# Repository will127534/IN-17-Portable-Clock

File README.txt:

This is a project of my NIXIE Clock
which uses four IN-17 in a 5cm x 3 cm size
and it can power by USB and build in 200mah Li-poly.

Blog(Chinese):http://will-123456.blogspot.tw/2015/03/in-17-nixie-tube-portable-clock.html
Hackaday.io :http://hackaday.io/project/5105-in-17-portable-clock

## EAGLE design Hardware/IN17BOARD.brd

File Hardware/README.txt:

Becareful about High Voltage and Li-poly battery

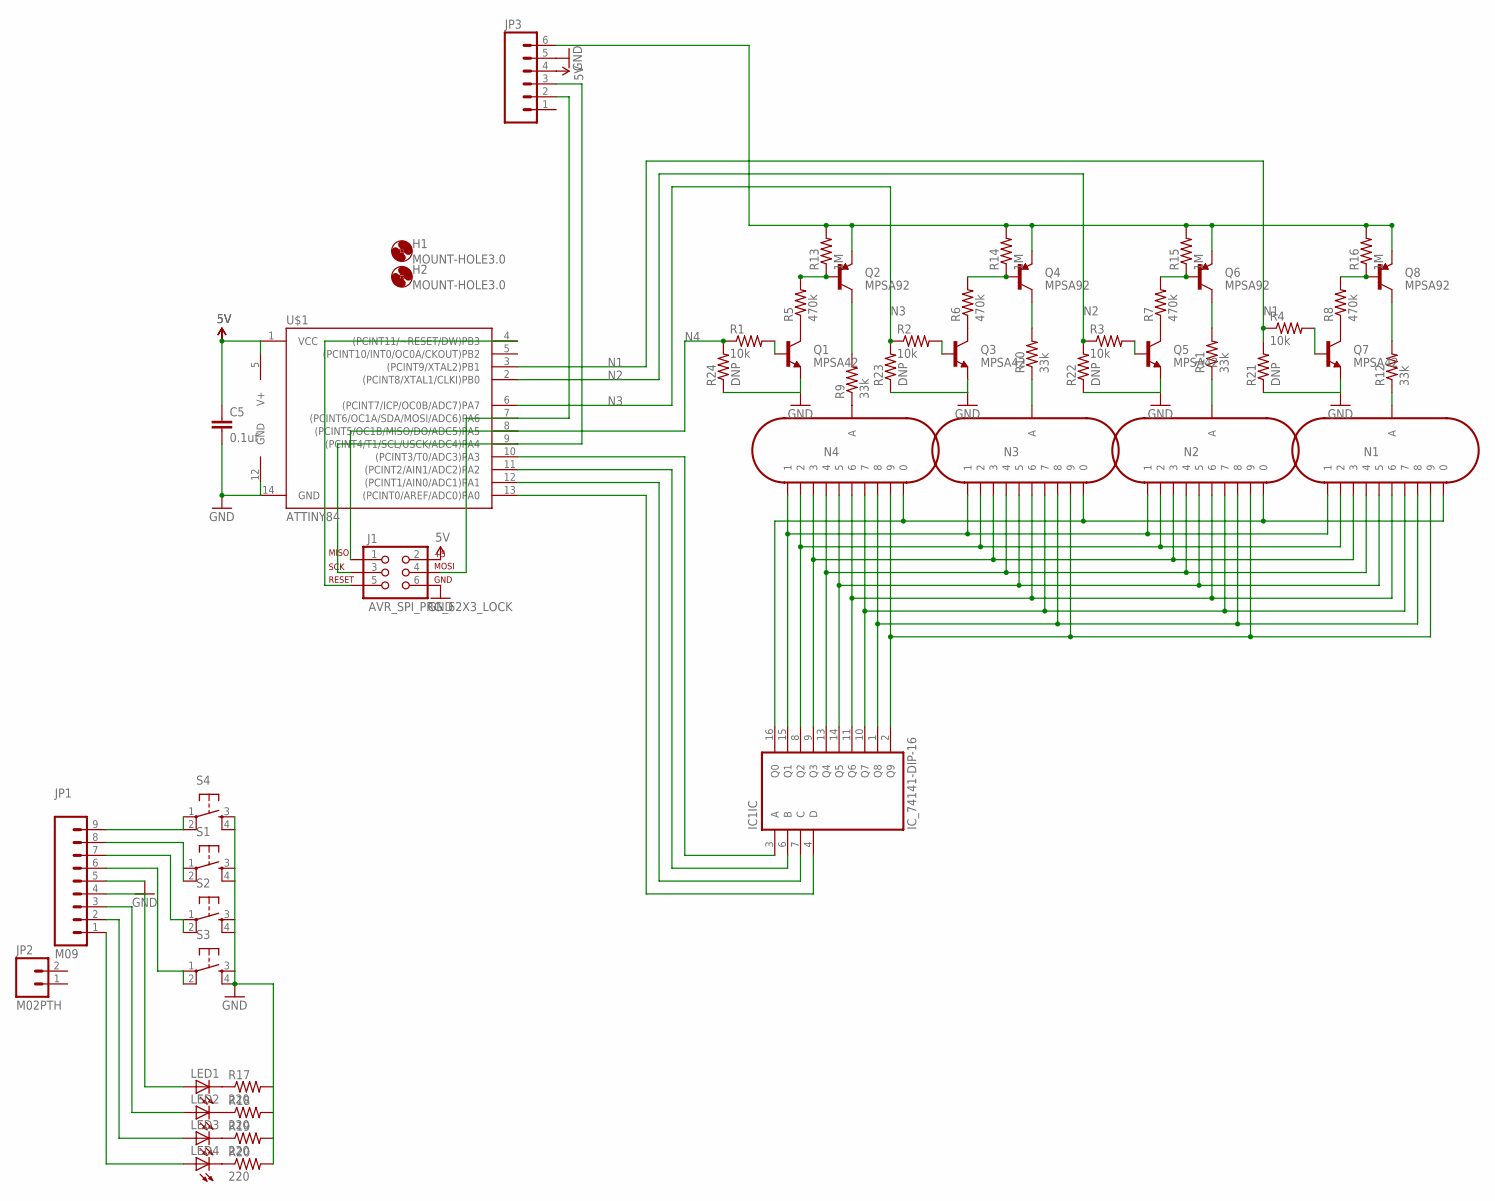
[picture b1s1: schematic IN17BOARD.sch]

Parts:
C5: 0.1uf; 0805
H1, H2: MOUNT-HOLE3.0; 3,0
IC1: IC_74141-DIP-16; DIL16
J1: AVR_SPI_PRG_62X3_LOCK; 2X3_LOCK
JP1: M09; 1X09
JP2: M02PTH; 1X02
JP3: M06SIP; 1X06
LED1, LED2, LED3, LED4: LED0603; LED-0603
N1, N2, N3, N4: IN-17
Q1, Q3, Q5, Q7: MPSA42; SOT23
Q2, Q4, Q6, Q8: MPSA92; SOT23
R1, R2, R3, R4: 10k; 0805
R5, R6, R7, R8: 470k; 0805
R9, R10, R11, R12: 33k; 0805
R13, R14, R15, R16: 1M; 0805
R17, R18, R19, R20: 220; 0603-RES
R21, R22, R23, R24: DNP; 0805
S1, S2, S3, S4: TAC_SWITCHPTH; TACTILE-PTH
U$1: ATTINY84; SO14

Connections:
0: IC1.16 (Q0), N1.0, N2.0, N3.0, N4.0
1: IC1.15 (Q1), N1.1, N2.1, N3.1, N4.1
2: IC1.8 (Q2), N1.2, N2.2, N3.2, N4.2
3: IC1.9 (Q3), N1.3, N2.3, N3.3, N4.3
4: IC1.13 (Q4), N1.4, N2.4, N3.4, N4.4
5: IC1.14 (Q5), N1.5, N2.5, N3.5, N4.5
5V: C5.1, IC1.5 (V+), J1.2, JP3.4, U$1.1 (VCC)
6: IC1.11 (Q6), N1.6, N2.6, N3.6, N4.6
7: IC1.10 (Q7), N1.7, N2.7, N3.7, N4.7
8: IC1.1 (Q8), N1.8, N2.8, N3.8, N4.8
9: IC1.2 (Q9), N1.9, N2.9, N3.9, N4.9
A: IC1.3 (A), U$1.10 ((PCINT3/T0/ADC3)PA3)
B: IC1.6 (B), U$1.11 ((PCINT2/AIN1/ADC2)PA2)
C: IC1.7 (C), U$1.12 ((PCINT1/AIN0/ADC1)PA1)
D: IC1.4 (D), U$1.13 ((PCINT0/AREF/ADC0)PA0)
GND: C5.2, IC1.12 (GND), J1.6, JP1.5, JP3.5, Q1.2 (E), Q3.2 (E), Q5.2 (E), Q7.2 (E), R17.2, R18.2, R19.2, R20.2, R21.1, R22.1, R23.1, R24.1, S1.3, S1.4, S2.3, S2.4, S3.3, S3.4, S4.3, S4.4, U$1.14 (GND)
N1: R4.1, R21.2, U$1.3 ((PCINT9/XTAL2)PB1)
N2: R3.1, R22.2, U$1.2 ((PCINT8/XTAL1/CLKI)PB0)
N3: R2.1, R23.2, U$1.6 ((PCINT7/ICP/OC0B/ADC7)PA7)
N4: J1.1, R1.1, R24.2, U$1.8 ((PCINT5/OC1B/MISO/DO/ADC5)PA5)
unnamed: J1.5, U$1.4 ((PCINT11/~RESET/DW)PB3)
unnamed: Q1.1 (B), R1.2
unnamed: Q3.1 (B), R2.2
unnamed: Q5.1 (B), R3.2
unnamed: Q7.1 (B), R4.2
unnamed: Q1.3 (C), R5.1
unnamed: Q3.3 (C), R6.1
unnamed: Q5.3 (C), R7.1
unnamed: Q7.3 (C), R8.1
unnamed: Q2.1 (B), R5.2, R13.1
unnamed: Q4.1 (B), R6.2, R14.1
unnamed: Q6.1 (B), R7.2, R15.1
unnamed: Q8.1 (B), R8.2, R16.1
unnamed: JP3.6, Q2.2 (E), Q4.2 (E), Q6.2 (E), Q8.2 (E), R13.2, R14.2, R15.2, R16.2
unnamed: N4.A, R9.1
unnamed: N3.A, R10.1
unnamed: N2.A, R11.1
unnamed: N1.A, R12.1
unnamed: Q2.3 (C), R9.2
unnamed: Q4.3 (C), R10.2
unnamed: Q6.3 (C), R11.2
unnamed: Q8.3 (C), R12.2
unnamed: LED1.C, R17.1
unnamed: LED2.C, R18.1
unnamed: LED3.C, R19.1
unnamed: JP1.9, S4.1, S4.2
unnamed: JP1.8, S1.1, S1.2
unnamed: JP1.7, S2.1, S2.2
unnamed: JP1.6, S3.2
unnamed: LED4.C, R20.1
unnamed: JP1.4, LED1.A
unnamed: JP1.3, LED2.A
unnamed: JP1.2, LED3.A
unnamed: JP1.1, LED4.A
SCL: J1.3, JP3.3, U$1.9 ((PCINT4/T1/SCL/USCK/ADC4)PA4)
SDA: J1.4, JP3.2, U$1.7 ((PCINT6/OC1A/SDA/MOSI/ADC6)PA6)

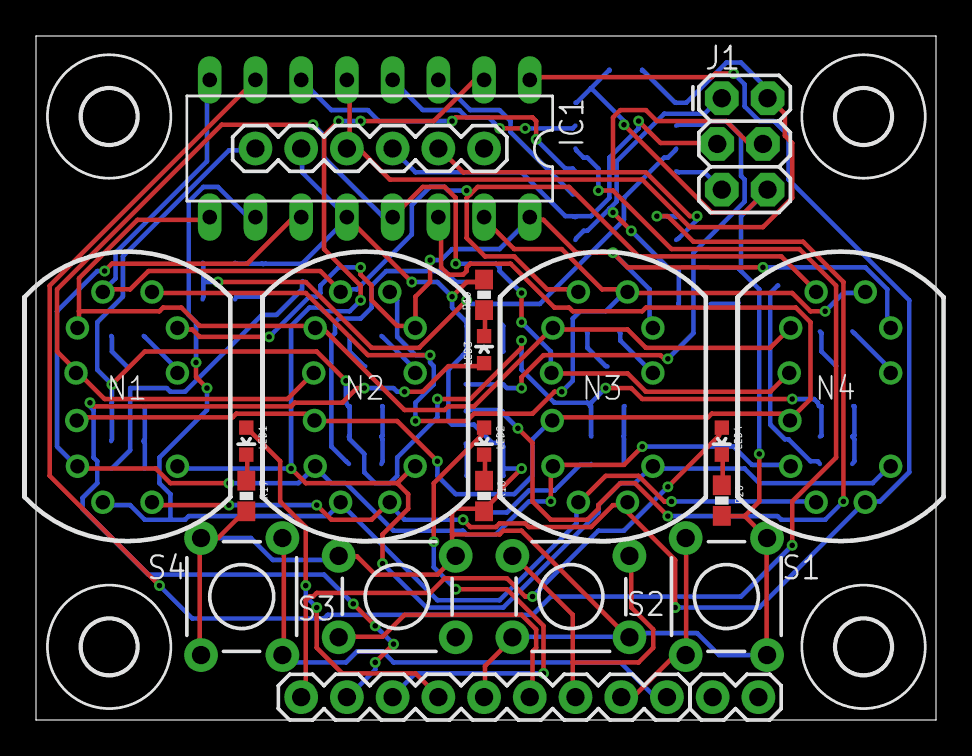
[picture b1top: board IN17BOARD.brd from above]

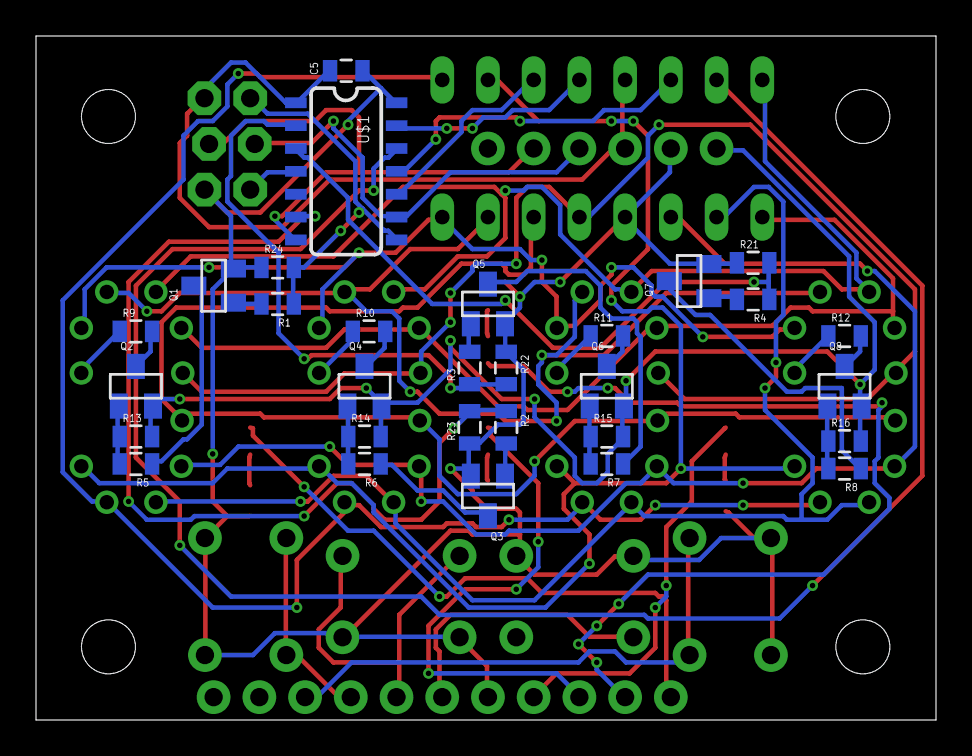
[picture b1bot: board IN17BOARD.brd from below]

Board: 2 copper layers, 50.0 x 38.0 mm, 55 parts (30 on the bottom side), 56 nets.

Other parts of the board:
H3, H4: MOUNT-HOLE3.0; 3,0

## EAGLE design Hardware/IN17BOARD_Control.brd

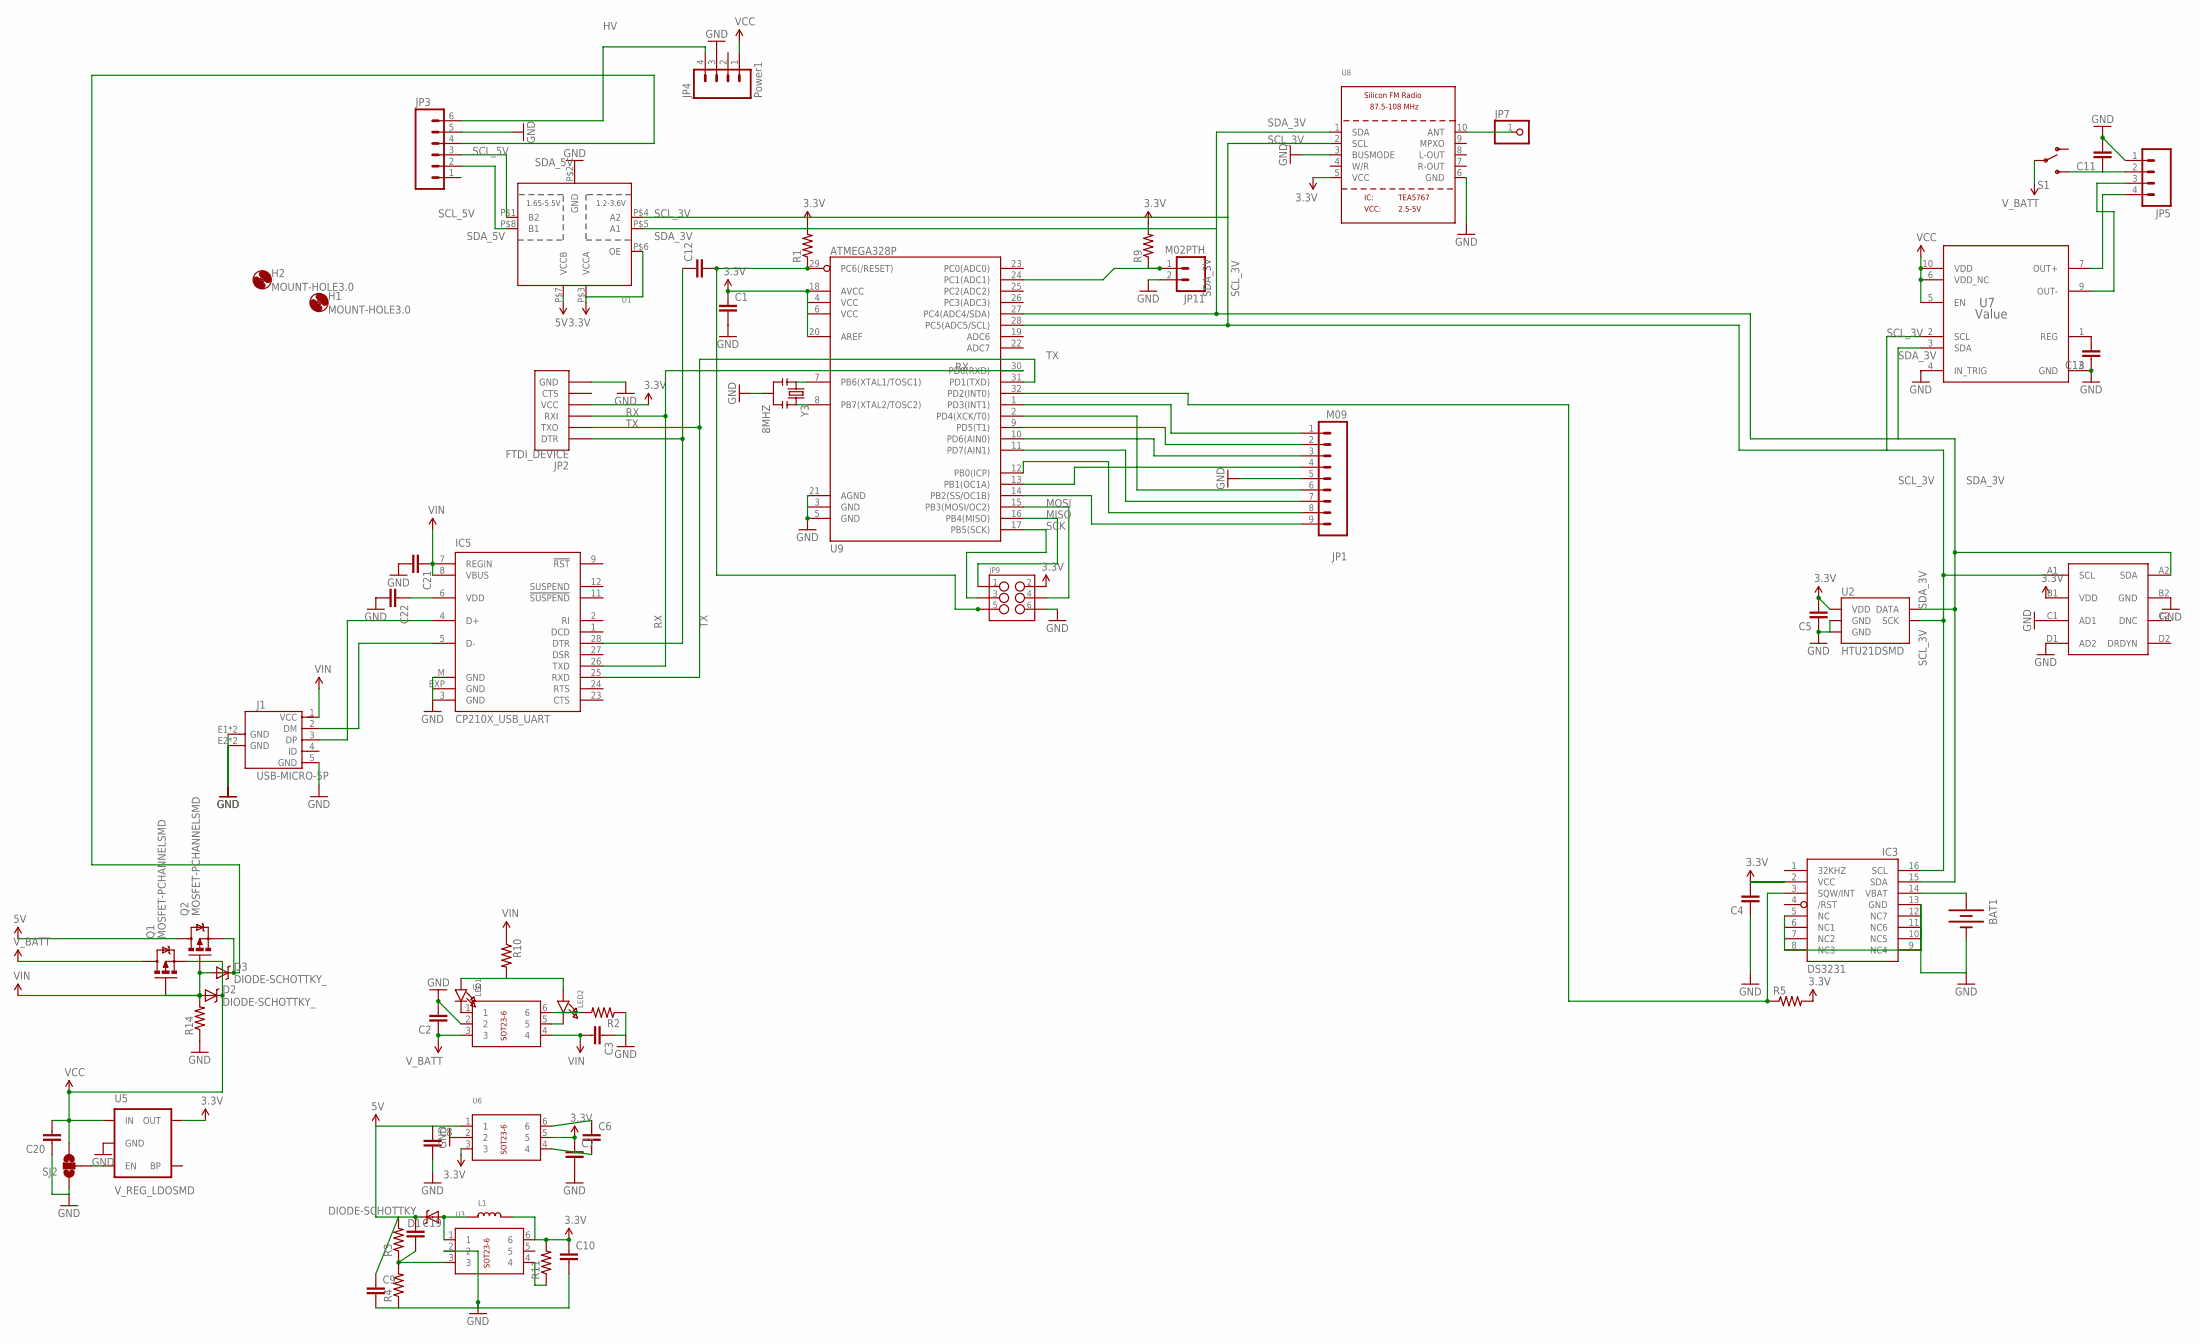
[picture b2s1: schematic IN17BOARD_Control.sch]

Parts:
BAT1: BATTERY12PTH; BATTCON_12MM_PTH
C1, C2, C3, C4, C5, C6, C7, C8, C9, C10, C11, C12, C13, C19, C20, C21, C22: CAP0805; 0805
D1, D2, D3: DIODE-SCHOTTKY_; SMA-DIODE
H1, H2: MOUNT-HOLE3.0; 3,0
IC3: DS3231/SO; SO16W
IC5: CP210X_USB_UART; MLP28
J1: USB-MICRO-5P; MICRO-USB-5P
JP1: M09; 1X09
JP2: FTDI_DEVICE; FTDI_DEVICE_SIDE
JP3: M06SIP; 1X06
JP4: Power1; 1X04_LOCK
JP5: M041.27MM; 1X04-1.27MM
JP7: HEADER-1X1ROUND; 1X01_ROUND
JP9: M03X22X3_SILK_SM; 2X3
JP11: M02PTH; 1X02
L1: INDUCTOR; INDUCTOR_1007
LED1, LED2: LED0603_NOOUTLINE; CHIPLED_0603_NOOUTLINE
Q1, Q2: MOSFET-PCHANNELSMD; SOT23-3
R1, R2, R3, R4, R5, R9, R10, R11, R14: RESISTOR0805-RES; 0805
S1: SWITCH-SPDT-SMD-A; SWITCH-SPST-SMD-A
SJ2: SOLDERJUMPER_2WAYS; SJ_3
U1: TXS0102; VFSOP-8
U2: HTU21DSMD; HTU21D
U3, U4, U6: BREAKOUT_SOT23-6
U5: V_REG_LDOSMD; SOT23-5
U7: Value; DGS0010A
U8: TEA5767MODULE
U9: ATMEGA328P; TQFP32-08
U$1: HDC1000; BGA
Y3: 8MHZ; RESONATOR-SMD

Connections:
3.3V: C1.1, C4.2, C5.2, C7.1, C10.1, C22.1, IC3.2 (VCC), IC5.6 (VDD), JP2.P$4 (VCC), JP9.2, L1.P$2 (2), R1.2, R5.2, R9.2, R11.2, U1.P$3 (VCCA), U1.P$6 (OE), U2.VDD, U3.6, U5.5 (OUT), U6.3, U6.5, U8.5 (VCC), U9.4 (VCC), U9.6 (VCC), U9.18 (AVCC), U9.20 (AREF), U$1.B1 (VDD)
5V: C8.1, C9.1, C19.1, D1.C, Q2.3 (D), R3.2, U1.P$7 (VCCB), U6.1
GND: BAT1.GND (-), C1.2, C2.2, C3.1, C4.1, C5.1, C7.2, C8.2, C9.2, C10.2, C11.2, C13.1, C20.1, C21.2, C22.2, IC3.5 (NC), IC3.6 (NC1), IC3.7 (NC2), IC3.8 (NC3), IC3.9 (NC4), IC3.10 (NC5), IC3.11 (NC6), IC3.12 (NC7), IC3.13 (GND), IC5.3 (GND), IC5.EXP (GND), IC5.M (GND), J1.5 (GND), J1.E1 (GND), J1.E2 (GND), J1.P1 (GND), J1.P2 (GND), JP1.5, JP2.P$6 (GND), JP3.5, JP4.3, JP5.1, JP9.6, JP11.2, R2.1, R4.1, R14.1, SJ2.1, U1.P$2 (GND), U2.7 (GND), U2.GND, U3.2, U4.2, U5.2 (GND), U6.2, U7.4 (IN_TRIG), U7.8 (GND), U8.3 (BUSMODE), U8.6 (GND), U9.3 (GND), U9.5 (GND), U9.21 (AGND), U$1.B2 (GND), U$1.C1 (AD1), U$1.D1 (AD2), Y3.2
HV: JP3.6, JP4.4
MISO: JP9.1, U9.16 (PB4(MISO))
MOSI: JP9.4, U9.15 (PB3(MOSI/OC2))
unnamed: C12.1, IC5.28 (DTR), JP2.P$1 (DTR)
unnamed: U9.8 (PB7(XTAL2/TOSC2)), Y3.3
unnamed: U9.7 (PB6(XTAL1/TOSC1)), Y3.1
unnamed: C11.1, JP5.2, S1.3 (S)
unnamed: BAT1.VCC@1 (+), IC3.14 (VBAT)
unnamed: C12.2, JP9.5, R1.1, U9.29 (PC6(/RESET))
unnamed: R2.2, U4.6
unnamed: IC3.3 (SQW/INT), R5.1, U9.32 (PD2(INT0))
unnamed: SJ2.2, U5.3 (EN)
unnamed: LED1.A, LED2.A, R10.2
unnamed: JP11.1, R9.1, U9.24 (PC1(ADC1))
unnamed: JP1.1, U9.1 (PD3(INT1))
unnamed: JP1.2, U9.9 (PD5(T1))
unnamed: JP1.3, U9.10 (PD6(AIN0))
unnamed: JP1.4, U9.13 (PB1(OC1A))
unnamed: C13.2, U7.1 (REG)
unnamed: JP5.3, U7.9 (OUT-)
unnamed: IC5.4 (D+), J1.3 (DP)
unnamed: JP1.6, U9.2 (PD4(XCK/T0))
unnamed: JP1.7, U9.11 (PD7(AIN1))
unnamed: JP1.8, U9.12 (PB0(ICP))
unnamed: JP1.9, U9.14 (PB2(SS/OC1B))
unnamed: JP7.1, U8.10 (ANT)
unnamed: IC5.5 (D-), J1.2 (DM)
unnamed: JP5.4, U7.7 (OUT+)
unnamed: D1.A, L1.P$1 (1), U3.1
unnamed: LED1.C, U4.1
unnamed: LED2.C, U4.5
unnamed: C6.2, U6.4
unnamed: C6.1, U6.6
unnamed: C19.2, R3.1, R4.2, U3.3
unnamed: R11.1, U3.4
unnamed: D3.C, JP3.4, Q2.2 (S)
RX: IC5.26 (TXD), JP2.P$3 (RXI), U9.30 (PD0(RXD))
SCK: JP9.3, U9.17 (PB5(SCK))
SCL_3V: IC3.16 (SCL), U1.P$4 (A2), U2.SCK, U7.2 (SCL), U8.2 (SCL), U9.28 (PC5(ADC5/SCL)), U$1.A1 (SCL)
SCL_5V: JP3.3, U1.P$1 (B2)
SDA_3V: IC3.15 (SDA), U1.P$5 (A1), U2.DATA, U7.3 (SDA), U8.1 (SDA), U9.27 (PC4(ADC4/SDA)), U$1.A2 (SDA)
SDA_5V: JP3.2, U1.P$8 (B1)
TX: IC5.25 (RXD), JP2.P$2 (TXO), U9.31 (PD1(TXD))
VCC: C20.2, D2.C, JP4.1, Q1.2 (S), SJ2.3, U5.1 (IN), U7.5 (EN), U7.6 (VDD_NC), U7.10 (VDD)
VIN: C3.2, C21.1, D2.A, D3.A, IC5.7 (REGIN), IC5.8 (VBUS), J1.1 (VCC), Q1.1 (G), Q2.1 (G), R10.1, R14.2, U4.4
V_BATT: C2.1, Q1.3 (D), S1.2, U4.3

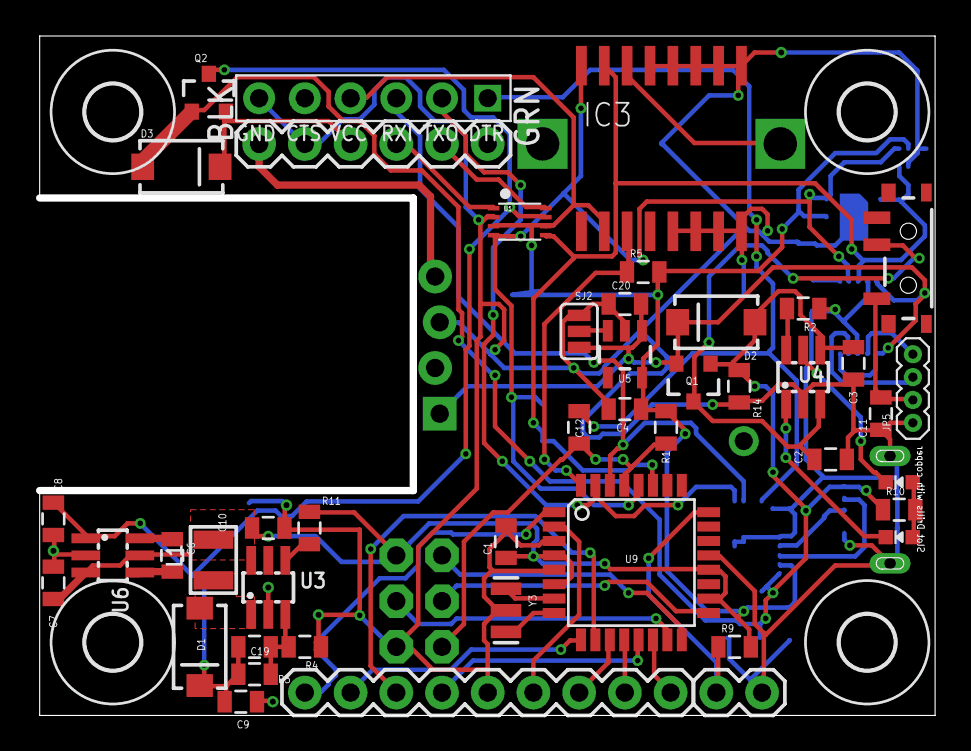
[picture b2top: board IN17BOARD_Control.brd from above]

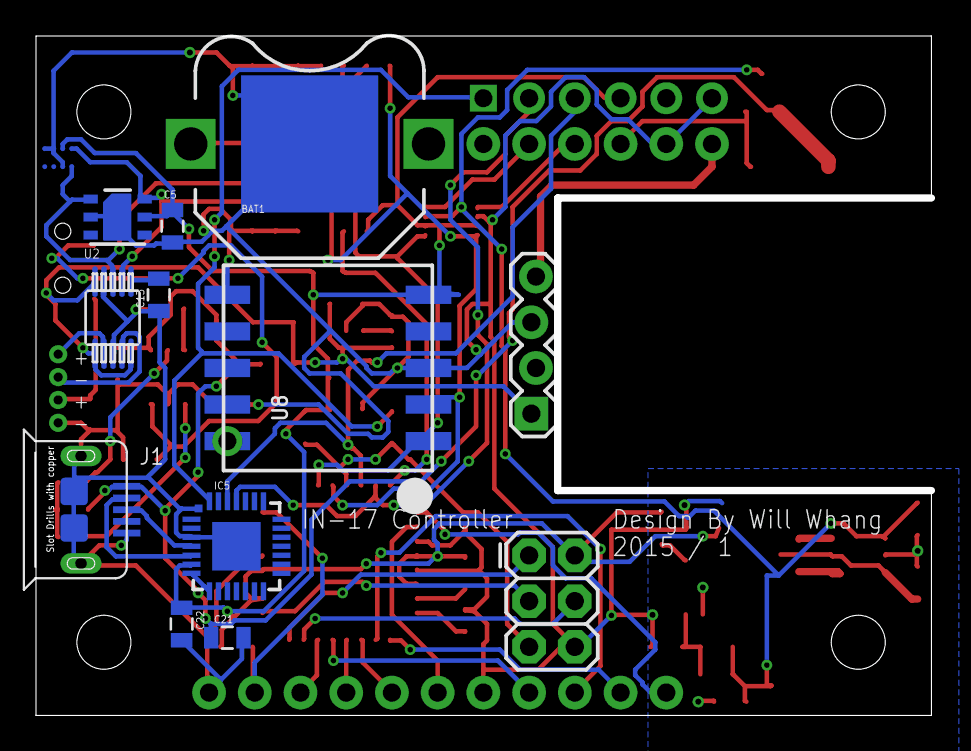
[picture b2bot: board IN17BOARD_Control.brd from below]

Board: 2 copper layers, 49.5 x 37.3 mm, 63 parts (13 on the bottom side), 49 nets.

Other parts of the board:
H3, H4: MOUNT-HOLE3.0; 3,0

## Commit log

2015-04-04 :boom::camel: Added .gitattributes & .gitignore files
2015-04-04 Uploaded Hardware files
2015-04-04 Update Blog & hackaday project
2015-04-07 Added IN-17 Display board firmware & PCB value
2015-04-10 Add value and main sketch

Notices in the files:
parts and their libraries:
SparkFun-DigitalIC: Licensing: CC v3.0 Share-Alike You are welcome to use this library for commercial purposes.
microbuilder: This work is placed in the public domain, and may be freely used for commercial and non-commercial work with the following conditions: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
